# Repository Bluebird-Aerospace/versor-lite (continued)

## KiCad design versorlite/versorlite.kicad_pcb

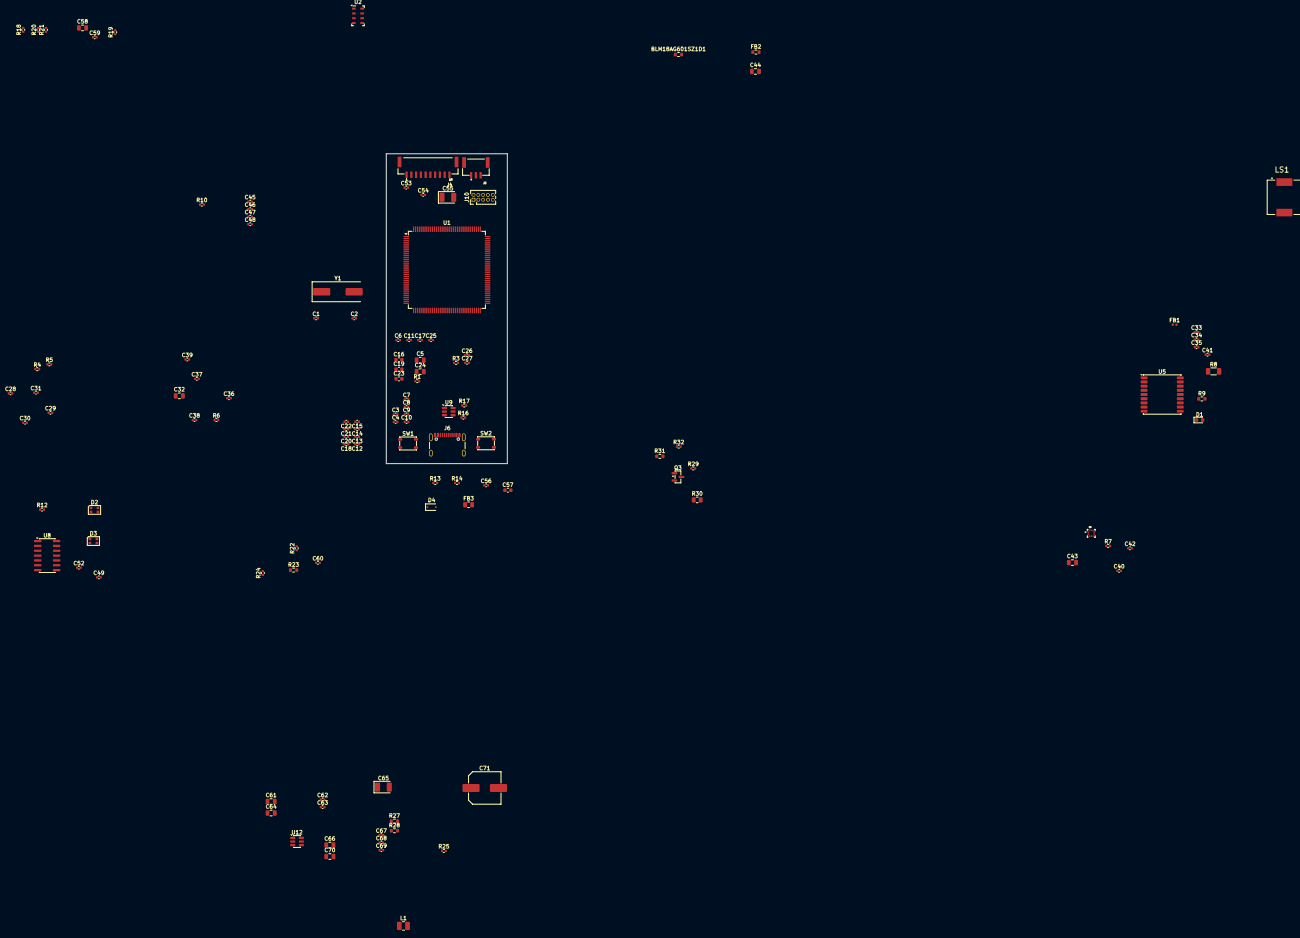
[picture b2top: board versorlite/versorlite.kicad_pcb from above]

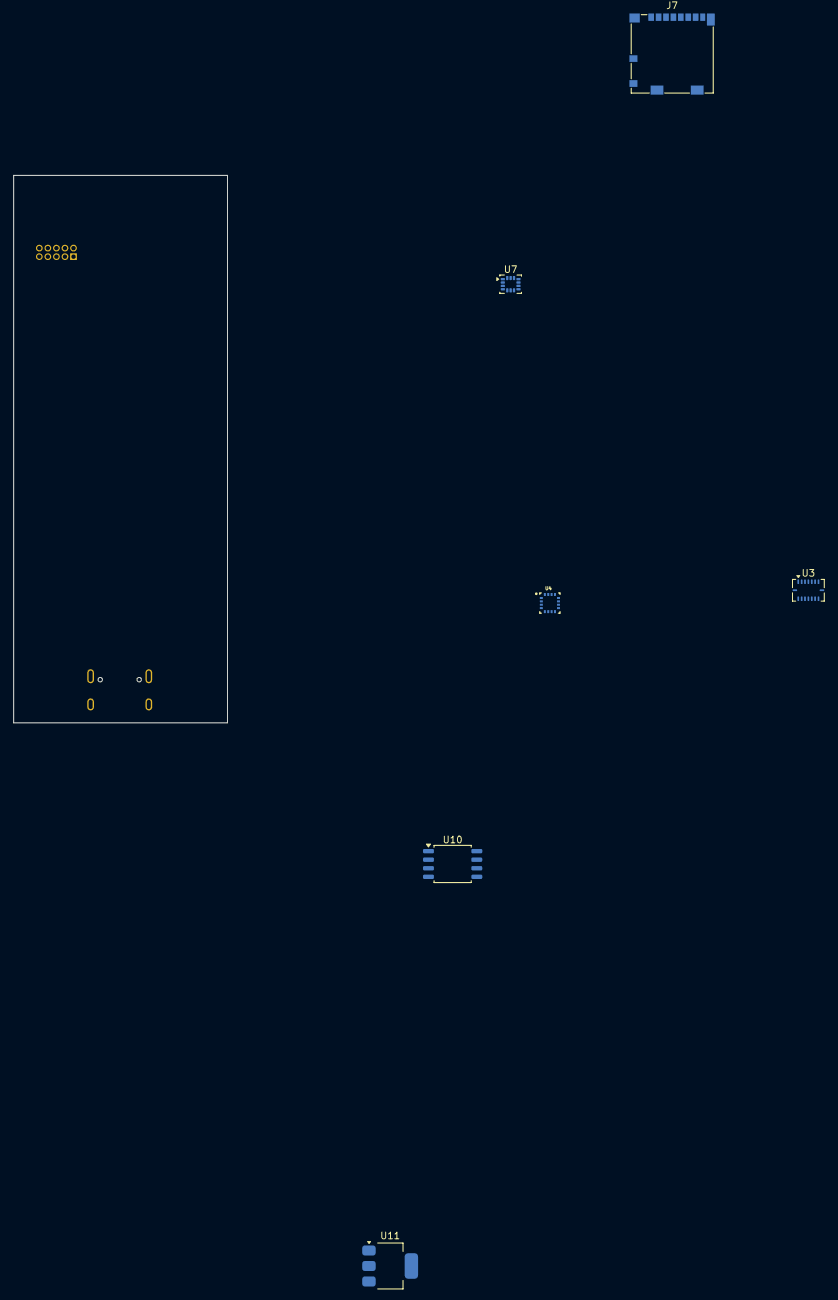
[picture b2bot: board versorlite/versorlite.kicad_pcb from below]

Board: 2 copper layers, 31.8 x 81.3 mm, 128 parts (6 on the bottom side), 75 nets, no tracks yet.

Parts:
BLM18AG601SZ1D1: Ferrite Bead; R_0603_1608Metric
C1, C2: 30pf; C_0402_1005Metric
C3, C4, C6, C7, C8, C9, C10, C11, C12, C13, C17, C20, C21, C22, C25, C27, C29, C31, C33, C34, C35, C36, C37, C40, C42, C46, C48, C59, C62, C63, C67, C68, C69: 100nf; C_0402_1005Metric
C5, C24, C58: 10uf; C_0805_2012Metric
C14, C49, C52, C53, C56: 100nF; C_0402_1005Metric
C15, C18: 10pF; C_0402_1005Metric
C16, C19: 2.2µf; C_0603_1608Metric
C23: 4.7uf; C_0603_1608Metric
C26, C28, C30, C38, C39, C45, C47: 1μf; C_0402_1005Metric
C32, C43, C44, C64: 10μf; C_0805_2012Metric
C41: 10nF X7R; C_0402_1005Metric
C54: 1μF; C_0402_1005Metric
C55: 100uF; CP_EIA-3528-21_Kemet-B
C57: 4.7uF; C_0603_1608Metric
C60: 22pF; C_0402_1005Metric
C61, C66, C70: 22μf; C_0805_2012Metric
C65: 100μf; CP_EIA-3528-21_Kemet-B
C71: 470uF; C_Elec_8x10.2
D1: LED; LED_0603_1608Metric
D2, D3: WS2812B-2020; LED_WS2812B-2020_PLCC4_2.0x2.0mm
D4: D_TVS; D_SOD-323F
FB1: LQG15HS27NJ02D; L_0402_1005Metric
FB2: BLM18AG601SZ1D; R_0603_1608Metric
FB3: FerriteBead_Small; R_0805_2012Metric
J4: RFD900ux 10 Pin Header; JST_BM10B-GHS-TBT_LF__SN__N_
J5: RFD900ux 3 Pin Power Select; CONN_BM03B-GHS-TBT_LF__SN__N_
J6: USB_C_Receptacle_USB2.0_16P; USB_C_Receptacle_GCT_USB4105-xx-A_16P_TopMnt_Horizontal
J7: Micro_SD_Card_Det2; microSD_HC_Molex_104031-0811
J10: Conn_ARM_JTAG_SWD_10; PinHeader_2x05_P1.27mm_Vertical
L1: CIGW252010GL4R7MNE, 4.7uH; L_1008_2520Metric
LS1: CPT-9019S-SMT; CUI_CPT-9019S-SMT
Q3: AO3400A; SOT-23
R1, R3, R4, R5, R6, R7, R10, R18, R19, R20, R21, R22, R24, R25: 10k; R_0402_1005Metric
R8: 10ohm, 0.25W; R_1206_3216Metric
R9: 1k; R_0603_1608Metric
R12: 470Ω; R_0402_1005Metric
R13, R14: 5.1k; R_0402_1005Metric
R16, R17: 22ohm; R_0402_1005Metric
R23: 10M; R_0603_1608Metric
R27: 100kΩ; R_0603_1608Metric
R28: 33kΩ; R_0603_1608Metric
R29, R32: 10kΩ; R_0402_1005Metric
R30: 1kΩ; R_0805_2012Metric
R31: 100Ω; R_0603_1608Metric
SW1, SW2: SW_Push; SW_SPST_PTS810
U1: STM32F407ZGTx; LQFP-144_20x20mm_P0.5mm
U2: MS5611-01BA; LGA-8_3x5mm_P1.25mm
U3: BMI088; Bosch_LGA-16_4.5x3mm_P0.5mm_LayoutBorder7x1y_ClockwisePinNu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
U4: MMC5983MA; PQFN50P300X300X100-16N
U5: MAX-M10S; ublox_MAX
U6: BMP388
U7: LSM6DSM; LGA-14_3x2.5mm_P0.5mm_LayoutBorder3x4y
U8: 74AHCT125; SOIC-14_3.9x8.7mm_P1.27mm
U9: WE-TVS-82400102; SOT-23-6
U10: W25Q128JVS; SOIC-8_5.3x5.3mm_P1.27mm
U11: LT1963AxST-3.3; SOT-223-3_TabPin2
U12: AP63205WU; TSOT-23-6
Y1: LFXTAL036869Reel 8MHz Crystal; Crystal_SMD_HC49-SD

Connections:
+3.3V_MAIN: BLM18AG601SZ1D1.1, C3.1, C4.1, C6.1, C7.1, C9.1, C10.1, C11.1, C12.1, C13.1, C17.1, C20.1, C21.1, C22.1, C23.2, C58.1, C59.1, C60.1, C61.2, C62.1, FB2.1, J7.4 (VDD), J10.1 (VTref), R18.1, R19.1, R20.2, R21.2, R22.1, R23.1, R24.1, R29.1, SW1.1, U1.6 (VBAT), U1.17 (VDD), U1.30 (VDD), U1.39 (VDD), U1.52 (VDD), U1.62 (VDD), U1.72 (VDD), U1.84 (VDD), U1.95 (VDD), U1.108 (VDD), U1.121 (VDD), U1.131 (VDD), U1.143 (PDR_ON), U1.144 (VDD), U10.8 (VCC), U11.3 (OUT)
+3V3_MCU: BLM18AG601SZ1D1.2, C5.1, C8.1, C24.1, C25.1, U1.32 (VREF+), U1.33 (VDDA)
+3V3_SENSORS: C26.1, C27.1, C28.1, C29.1, C30.2, C31.2, C33.2, C34.2, C35.2, C36.1, C37.2, C38.1, C39.2, C40.1, C42.2, C43.1, C44.1, C45.1, C46.1, C47.2, C48.2, FB2.2, R3.2, R4.2, R5.2, R6.2, R7.2, R10.2, U2.1 (VDD), U3.3 (VDD), U3.11 (VDDIO), U4.2 (VDD), U4.13 (VDDIO), U5.6 (V_BCKP), U5.7 (VCC_IO), U5.8 (VCC), U5.15 (VIO_SEL), U6.1 (VDDIO), U6.10 (VDD), U7.5 (VDDIO), U7.8 (VDD)
+5V: C49.1, C52.2, C53.1, C54.1, C55.1, C63.2, C64.1, D2.4 (VDD), D3.4 (VDD), J4.2 (VEXT), U8.14 (VCC), U11.1 (IN)
/MCU/BATT_READ: R27.2, R28.1, U1.26 (PC0)
/MCU/BUZZ_TIM9_CH1: LS1.2, U1.4 (PE5)
/MCU/CS_BARO_HIGH: R3.1, U1.64 (PE11), U2.4 (CSB), U2.5 (CSB)
/MCU/CS_BARO_LOW: R7.1, U1.63 (PE10), U6.6 (CSB)
/MCU/CS_IMU_HIGHG: R10.1, U1.65 (PE12), U7.12 (CS)
/MCU/CS_IMU_LOWG_ACCEL: R5.1, U1.59 (PE8), U3.14 (~CSB1)
/MCU/CS_IMU_LOWG_GYRO: R4.1, U1.60 (PE9), U3.5 (~CSB2)
/MCU/CS_MAG: R6.1, U1.58 (PE7), U4.4 (~SPI_CS)
/MCU/D+: R17.2, U1.104 (PA12)
/MCU/D-: R16.2, U1.103 (PA11)
/MCU/EXTI0_BARO_LOW: U1.56 (PG0), U6.7 (INT)
/MCU/EXTI1_IMU_LOWG_ACCEL: U1.57 (PG1), U3.16 (INT1)
/MCU/EXTI2_IMU_LOWG_GYRO: U1.87 (PG2), U3.12 (INT3)
/MCU/EXTI3_IMU_HIGHG: U1.88 (PG3), U7.4 (INT1)
/MCU/EXTI4_MAG: U1.89 (PG4), U4.15 (INT)
/MCU/GPS_RESET: U1.10 (PF0), U5.9 (~RESET)
/MCU/IGN_ADC: R29.2, U1.18 (PF6)
/MCU/IGN_SIG: R31.2, U1.12 (PF2)
/MCU/LED_TIM2_CH1: U1.34 (PA0), U8.2
/MCU/MICRO_SD_DETECT: J7.10 (DET_A), R19.2, U1.50 (PF12)
/MCU/NRST: C14.2, J10.10 (~RESET), SW2.1, U1.25 (NRST)
/MCU/OSC_IN: C1.1, C15.2, U1.23 (PH0), Y1.1
/MCU/OSC_OUT: C2.1, C18.2, U1.24 (PH1), Y1.2
/MCU/RADIO_GPIO: J4.4 (GPIO1), U1.86 (PD15)
/MCU/SPI1_MISO: U1.42 (PA6), U2.6 (SDO), U3.10 (SDO2), U3.15 (SDO1), U4.5 (SPI_SDO), U6.5 (SDO), U7.1 (SDO/SA0)
/MCU/SPI1_MOSI: U1.43 (PA7), U2.7 (SDI/SDA), U3.9 (SDI/SDA), U4.16 (SDA/SPI_SDI), U6.4 (SDI), U7.14 (SDA)
/MCU/SPI1_SCK: U1.41 (PA5), U2.8 (SCLK), U3.8 (SCK/SCL), U4.1 (SCL/SPI_SCK), U6.2 (SCK), U7.13 (SCL)
/MCU/SPI2_MISO: J7.7 (DAT0), R21.1, U1.28 (PC2), U10.2 (DO/IO_{1})
/MCU/SPI2_MOSI: J7.3 (CMD), U1.29 (PC3), U10.5 (DI/IO_{0})
/MCU/SPI2_NSS_FLASH: R22.2, U1.140 (PB9), U10.1 (~CS)
/MCU/SPI2_NSS_MICROSD: J7.2 (DAT3/CD), R18.2, U1.73 (PB12)
/MCU/SPI2_SCK: J7.5 (CLK), U1.74 (PB13), U10.6 (CLK)
/MCU/SWCLK: J10.4 (SWCLK/TCK), U1.109 (PA14)
/MCU/SWDIO: J10.2 (SWDIO/TMS), U1.105 (PA13)
/MCU/UART4_RX_GPS: U1.112 (PC11), U5.2 (TXD)
/MCU/UART4_TX_GPS: U1.111 (PC10), U5.3 (RXD)
/MCU/USART2_CTS_RADIO: J4.8 (RTS), U1.117 (PD3)
/MCU/USART2_RTS_RADIO: J4.9 (CTS), U1.118 (PD4)
/MCU/USART2_RX_RADIO: J4.7 (TX), U1.37 (PA3)
/MCU/USART2_TX_RADIO: J4.6 (RX), U1.36 (PA2)
GND: C1.2, C2.2, C3.2, C4.2, C5.2, C6.2, C7.2, C8.2, C9.2, C10.2, C11.2, C12.2, C13.2, C14.1, C15.1, C16.2, C17.2, C18.1, C19.2, C20.2, C21.2, C22.2, C23.1, C24.2, C25.2, C26.2, C27.2, C28.2, C29.2, C30.1, C31.1, C32.1, C33.1, C34.1, C35.1, C36.2, C37.1, C38.2, C39.1, C40.2, C41.1, C42.1, C43.2, C44.2, C45.2, C46.2, C47.1, C48.1, C49.2, C52.1, C53.2, C54.2, C55.2, C56.2, C57.2, C58.2, C59.2, C60.2, C61.1, C62.2, C63.1, C64.2, C65.1, C66.1, C67.2, C69.2, C70.1, C71.2, D2.2 (VSS), D3.2 (VSS), D4.2 (A2), J4.1 (GND), J4.3 (GND), J4.10 (GND), J4.S1 (SHIELD), J4.S2 (SHIELD), J5.4 (SHIELD), J5.5 (SHIELD), J6.A1 (GND), J6.A12 (GND), J6.B1 (GND), J6.B12 (GND), J7.6 (VSS), J7.9 (DET_B), J10.3 (GND), J10.5 (GND), J10.9 (GNDDetect), LS1.1, R1.1, R9.2, R13.2, R14.2, R25.2, R28.2, R32.2, SW2.2, U1.16 (VSS), U1.31 (VSSA), U1.38 (VSS), U1.51 (VSS), U1.61 (VSS), U1.83 (VSS), U1.94 (VSS), U1.107 (VSS), U1.120 (VSS), U1.130 (VSS), U2.2 (PS), U2.3 (GND), U3.2 (GNDA), U3.4 (GNDA), U3.6 (GNDIO), U3.7 (PS), U4.9 (GND), U4.11 (GND), U5.1 (GND), U5.5 (EXTINT), U5.10 (GND), U5.12 (GND), U6.3 (VSS), U6.8 (VSS), U6.9 (VSS), U7.2 (SDX), U7.3 (SCX), U7.6 (GND), U7.7 (GND), U8.1, U8.4, U8.5, U8.7 (GND), U8.9, U8.10, U8.12, U8.13, U9.2, U10.4 (GND), U11.2 (GND), U12.4 (GND)
unnamed: C41.2, FB1.1, R8.2
unnamed: D1.2 (A), U5.4 (TIMEPULSE)
unnamed: D1.1 (K), R9.1
unnamed: D2.3 (DIN), R12.2
unnamed: D2.1 (DOUT), D3.3 (DIN)
unnamed: D4.1 (A1), FB3.2, J6.A4 (VBUS), J6.A9 (VBUS), J6.B4 (VBUS), J6.B9 (VBUS), U9.5
unnamed: C56.1, C57.1, FB3.1
unnamed: FB1.2, U5.11 (RF_IN)
unnamed: J5.1 (VEXT), J5.2 (SUPPLY)
unnamed: J6.A5 (CC1), R13.1
unnamed: J6.B5 (CC2), R14.1
unnamed: J6.A6 (D+), J6.B6 (D+), U9.3
unnamed: J6.A7 (D-), J6.B7 (D-), U9.1
unnamed: J7.1 (DAT2), J7.8 (DAT1), R20.1
unnamed: Q3.2 (S), R30.2
unnamed: C65.2, C66.2, C67.1, L1.1, U12.1 (FB)
unnamed: C69.1, C70.2, C71.1, R27.1, U12.2 (EN), U12.3 (IN)
unnamed: Q3.1 (G), R31.1, R32.1
unnamed: R12.1, U8.3
unnamed: R16.1, U9.6
unnamed: R17.1, U9.4
unnamed: R1.2, SW1.2, U1.138 (BOOT0)
unnamed: C16.1, U1.71 (VCAP_1)
unnamed: C19.1, U1.106 (VCAP_2)
unnamed: C32.2, U4.10 (CAP)
unnamed: R8.1, U5.14 (VCC_RF)
unnamed: R23.2, U10.7 (~HOLD/~RESET/IO_{3})
unnamed: R24.2, U10.3 (~WP/IO_{2})
unnamed: C68.2, U12.6 (BST)
unnamed: C68.1, L1.2, U12.5 (SW)

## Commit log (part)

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2026-04-22 versor lite copied
2026-04-23 add gitignore, rm extra git repo, switch mcu
2026-04-23 Fix PCB conflict (pls work)
2026-04-23 reset symbol annotations
2026-04-23 Component placement
2026-04-23 Place components; optimize spacing
2026-04-23 Flip MMC, pending install
2026-04-23 Test second GND fill zone
2026-04-24 make schematic changes
2026-04-24 Rearrange board for flexibility
2026-04-24 add footprint
2026-04-25 Rearrange PCB
2026-04-25 Improve spacing on LED and crystal
2026-04-25 Sensor decoupling capacitor placement
2026-04-25 More component arrangement
2026-04-25 Switch buzzer p/n
    No footprint yet
2026-04-25 VBUS, BMS diodes and fuses
2026-04-26 Test route, place some GND vias
2026-04-26 Remove obsolete footprint
2026-04-26 That was NOT supposed to be there
2026-04-26 GND layer to In2 in stackup
2026-04-26 Rearrange GNSS and sensors
2026-04-26 Use more robust terminal block
2026-04-27 Repair some traces
2026-04-27 Place vias for all MCU pins
2026-04-27 Routing MCU
2026-04-27 move decaps
2026-04-28 switch uart, usart, spi lines, adc, pwm
2026-04-28 switch sensor interrupts
2026-04-28 changed led, tim
2026-04-28 complete rest of pin swaps
2026-04-28 Rearrange
2026-04-28 Route some traces
2026-04-28 more pcb stuff:
2026-04-29 Route
2026-04-29 Route part 2
2026-04-29 Complete initial routing
2026-04-29 oop missed two traces
2026-04-29 Quick edits, authors
2026-04-29 Add second pyro channel
2026-04-29 Connect IGN2 signal, rearrange
2026-04-30 fix mosfet, power traces, remove capacitors
2026-04-30 fix mcu decaps
2026-04-30 Address all non-footprint DRC errors
2026-04-30 Remove temporary lock
2026-04-30 Fix silkscreen readability
2026-04-30 impedance match u.fl line
2026-04-30 fix mcc, gps decaps
2026-04-30 fix lsm decaps
2026-05-01 fix unconnected
2026-05-01 Move switch back to front
2026-05-01 add ideal diode
2026-05-01 add dedicated power switching
2026-05-01 add ign_adc2
2026-05-01 add pwm tht hole
2026-05-01 work on pcb drc errors
2026-05-01 more drc fixing
2026-05-01 fix more clearance violations
2026-05-01 drc errors -> 0
2026-05-01 add two more pwm holes
2026-05-01 fix drc warning errors
2026-05-01 more drc stuff
2026-05-01 size polyfuse, final drc stuff
2026-05-01 fix broken traces
2026-05-01 fix thermal vias
2026-05-01 fix thermal spoking
2026-05-01 spacing
2026-05-01 Give the switches proper names
2026-05-01 better schematic labeling so that mr. dzula isn't confused
2026-05-01 add 3d models
2026-05-01 impedance matching: update width, ground stitching
2026-05-02 update impedance matching and gnd stitching according to jlcpcb calculator
2026-05-02 impedance mistake
2026-05-02 rm 10pf caps, add 33pf caps close to mcu pins
2026-05-02 replace crystal with smaller, lower esr one, redo footprints, traces
2026-05-02 fix ign
2026-05-02 fix pyro adc
2026-05-02 connect pyro to fuse
2026-05-02 more jlcpcb, change jst gh header
2026-05-02 Curve GPS trace, fix DRC
2026-05-04 fix pyro channel
2026-05-04 more jlcpcb parts added
2026-05-04 Fix some alignments
2026-05-04 jlcstuffs
2026-05-04 switch buck converter
2026-05-04 Adjust more spacing
2026-05-04 Quick fix on some routing
2026-05-04 fix schem for buck conv
2026-05-05 replace buck converter on pcb
2026-05-05 fix buzzer
2026-05-05 fill out footprints
2026-05-05 more footprints
2026-05-05 JLCPCB LIBRARY IS COMPLETE
2026-05-05 refill zone
2026-05-06 replace stm, pin header
2026-05-07 change diode
2026-05-08 final jlcpcb update
2026-05-08 Adjust naming
2026-05-08 fix xt30
2026-05-27 update problem with build
2026-05-27 change board constraint trace width to 5 mil
2026-05-28 replace sensor to lsm6dsv320x
2026-05-29 jlcpcb fixes
2026-05-30 Sync impedance requirement doc to git
